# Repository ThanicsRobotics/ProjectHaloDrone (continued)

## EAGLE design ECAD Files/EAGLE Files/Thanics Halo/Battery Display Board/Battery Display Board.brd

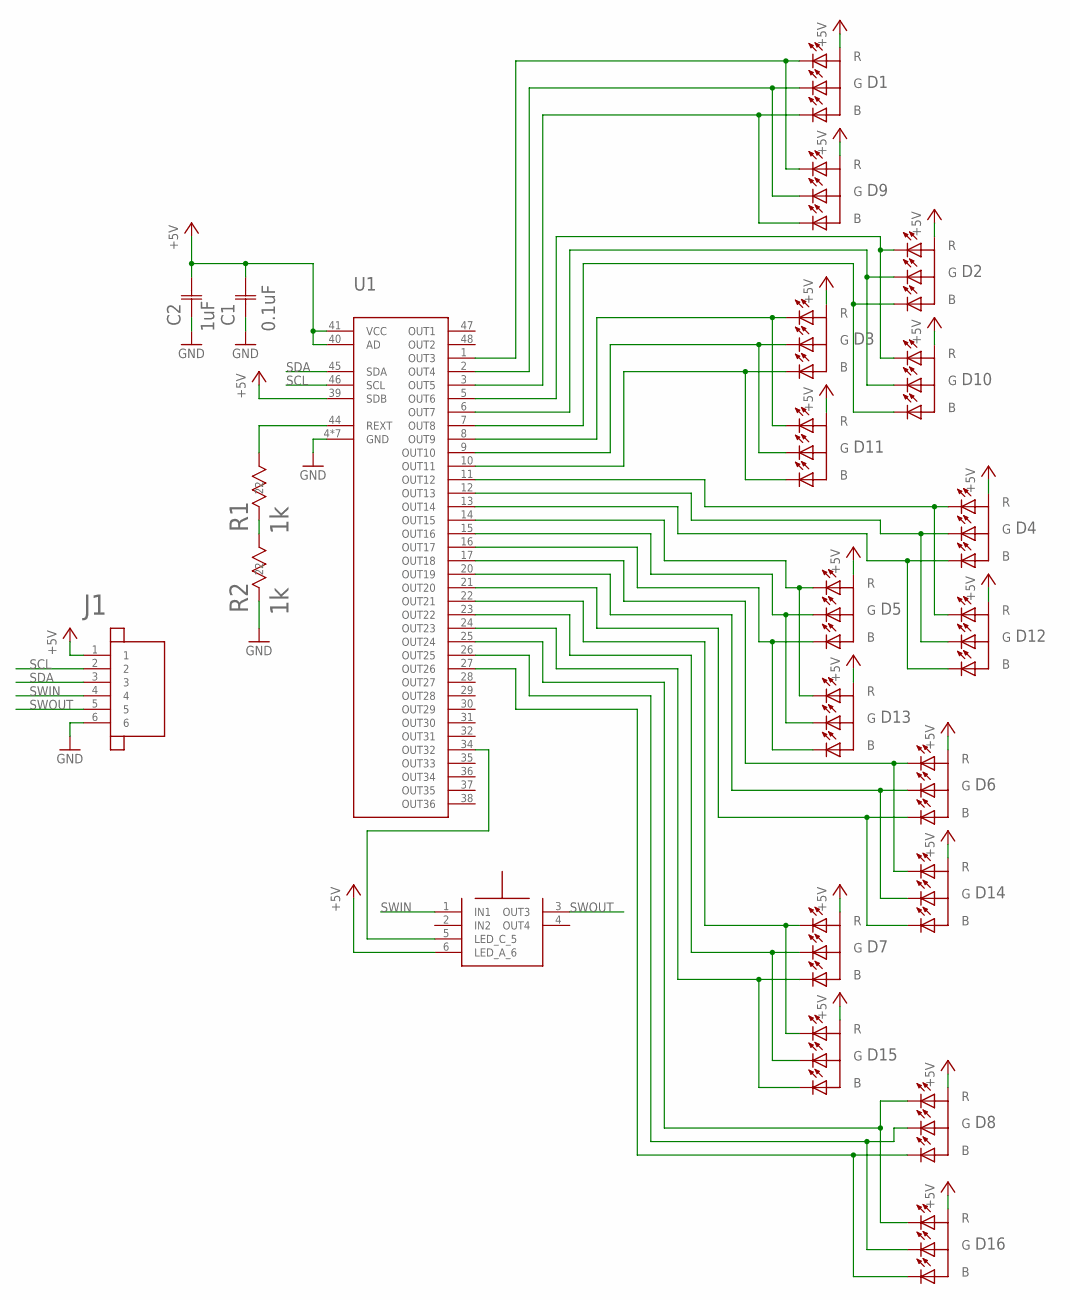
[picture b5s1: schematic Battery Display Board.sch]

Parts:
C1: 0.1uF; 0805
C2: 1uF; YAG_CC0805
D1, D2, D3, D4, D5, D6, D7, D8, D9, D10, D11, D12, D13, D14, D15, D16: ASMB-MTB0-0A3A2; ASMB-MTB0_LED
J1: JST_SH_6POS_SIDE
R1, R2: 1k; RC0603N-M
U1: IS31FL3236; TQFP-48
U$2: LED_TACT_SWITCH

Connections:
+5V: C1.2, C2.2 (22), D1.1 (A), D2.1 (A), D3.1 (A), D4.1 (A), D5.1 (A), D6.1 (A), D7.1 (A), D8.1 (A), D9.1 (A), D10.1 (A), D11.1 (A), D12.1 (A), D13.1 (A), D14.1 (A), D15.1 (A), D16.1 (A), J1.1, U1.39 (SDB), U1.40 (AD), U1.41 (VCC), U$2.6 (LED_A_6)
GND: C1.1, C2.1 (11), J1.6, R2.2 (22), U1.4 (GND), U1.18 (GND), U1.19 (GND), U1.33 (GND), U1.42 (GND), U1.43 (GND), U1.EP (GND)
unnamed: D1.4 (R), D9.4 (R), U1.1 (OUT3)
unnamed: D1.3 (G), D9.3 (G), U1.2 (OUT4)
unnamed: D2.3 (G), D10.3 (G), U1.6 (OUT7)
unnamed: D1.2 (B), D9.2 (B), U1.3 (OUT5)
unnamed: D2.4 (R), D10.4 (R), U1.5 (OUT6)
unnamed: R1.1 (11), U1.44 (REXT)
unnamed: D3.4 (R), D11.4 (R), U1.8 (OUT9)
unnamed: D3.3 (G), D11.3 (G), U1.9 (OUT10)
unnamed: D3.2 (B), D11.2 (B), U1.10 (OUT11)
unnamed: D4.4 (R), D12.4 (R), U1.11 (OUT12)
unnamed: D4.3 (G), D12.3 (G), U1.12 (OUT13)
unnamed: D4.2 (B), D12.2 (B), U1.13 (OUT14)
unnamed: D5.4 (R), D13.4 (R), U1.14 (OUT15)
unnamed: D5.3 (G), D13.3 (G), U1.15 (OUT16)
unnamed: D5.2 (B), D13.2 (B), U1.16 (OUT17)
unnamed: D6.4 (R), D14.4 (R), U1.17 (OUT18)
unnamed: D6.3 (G), D14.3 (G), U1.20 (OUT19)
unnamed: D6.2 (B), D14.2 (B), U1.21 (OUT20)
unnamed: D7.4 (R), D15.4 (R), U1.22 (OUT21)
unnamed: D7.3 (G), D15.3 (G), U1.23 (OUT22)
unnamed: D7.2 (B), D15.2 (B), U1.24 (OUT23)
unnamed: D8.4 (R), D16.4 (R), U1.25 (OUT24)
unnamed: D8.3 (G), D16.3 (G), U1.26 (OUT25)
unnamed: D8.2 (B), D16.2 (B), U1.27 (OUT26)
unnamed: D2.2 (B), D10.2 (B), U1.7 (OUT8)
unnamed: R1.2 (22), R2.1 (11)
unnamed: U1.34 (OUT32), U$2.5 (LED_C_5)
SCL: J1.2, U1.46 (SCL)
SDA: J1.3, U1.45 (SDA)
SWIN: J1.4, U$2.1 (IN1)
SWOUT: J1.5, U$2.3 (OUT3)

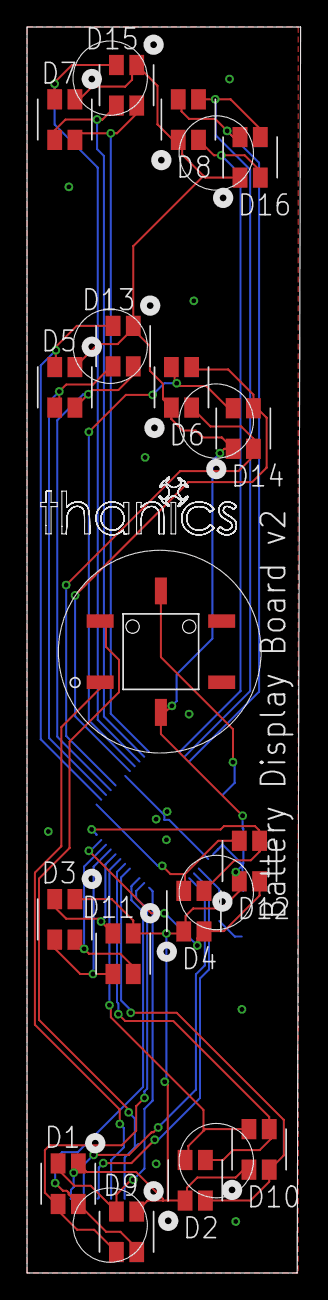
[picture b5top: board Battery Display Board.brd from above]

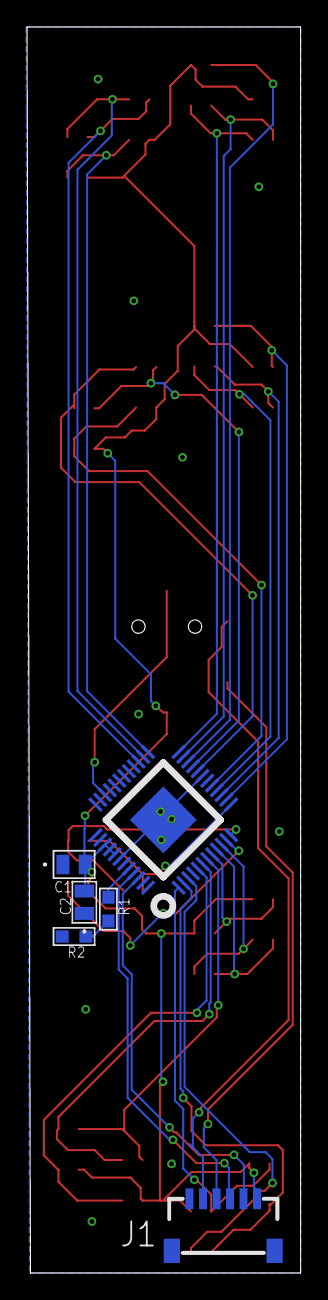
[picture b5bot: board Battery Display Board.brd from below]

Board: 2 copper layers, 20.2 x 92.2 mm, 23 parts (6 on the bottom side), 33 nets.

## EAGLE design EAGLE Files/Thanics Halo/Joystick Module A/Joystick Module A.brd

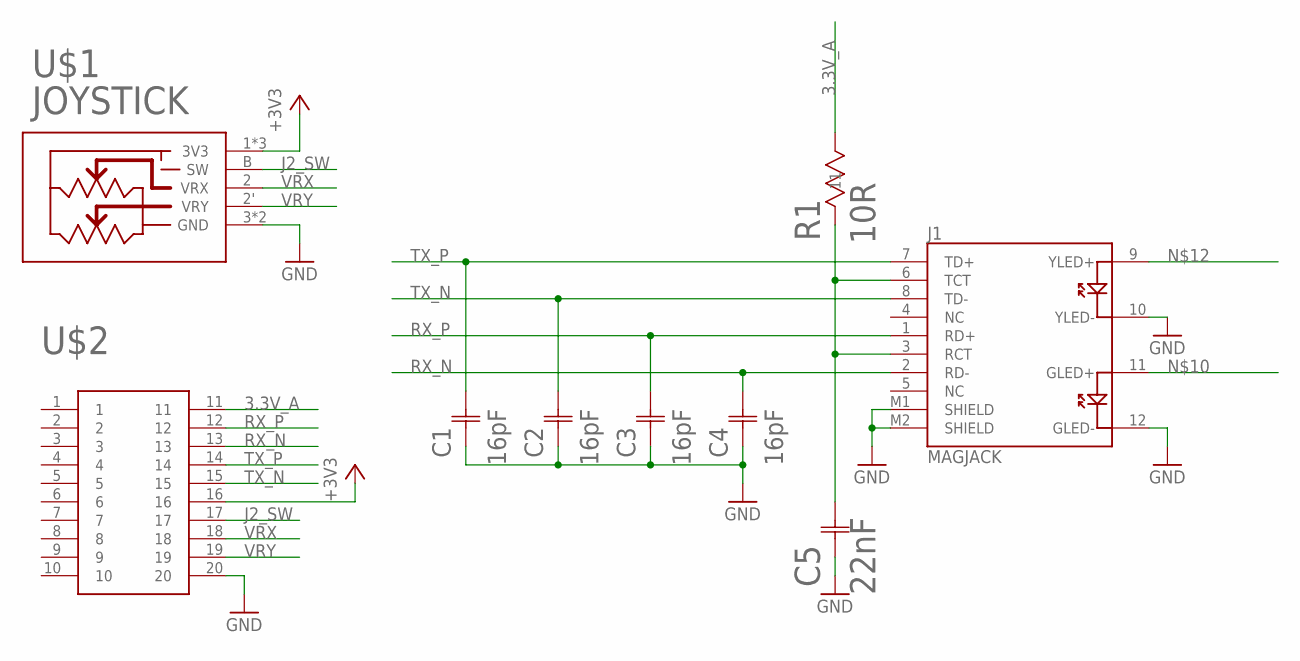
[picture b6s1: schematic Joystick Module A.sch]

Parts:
C1, C2, C3, C4: 16pF; G-155-M
C5: 22nF; G-155-M
J1: MAGJACK
R1: 10R; STA_RNCP0805-M
U$1: JOYSTICK"; JOYSTICK
U$2: EDGE_CONNECTOR_20POS_CONTACTS

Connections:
3.3V_A: R1.2 (22), U$2.11
+3V3: U$1.1 (3V3), U$1.1' (3V3), U$1.A (3V3), U$2.16
GND: C1.1 (11), C2.1 (11), C3.1 (11), C4.1 (11), C5.1 (11), J1.10 (YLED-), J1.12 (GLED-), J1.M1 (SHIELD), J1.M2 (SHIELD), U$1.3 (GND), U$1.3' (GND), U$2.20
J2_SW: U$1.B (SW), U$2.17
unnamed: C5.2 (22), J1.3 (RCT), J1.6 (TCT), R1.1 (11)
RX_N: C4.2 (22), J1.2 (RD-), U$2.13
RX_P: C3.2 (22), J1.1 (RD+), U$2.12
TX_N: C2.2 (22), J1.8 (TD-), U$2.15
TX_P: C1.2 (22), J1.7 (TD+), U$2.14
VRX: U$1.2 (VRX), U$2.18
VRY: U$1.2' (VRY), U$2.19

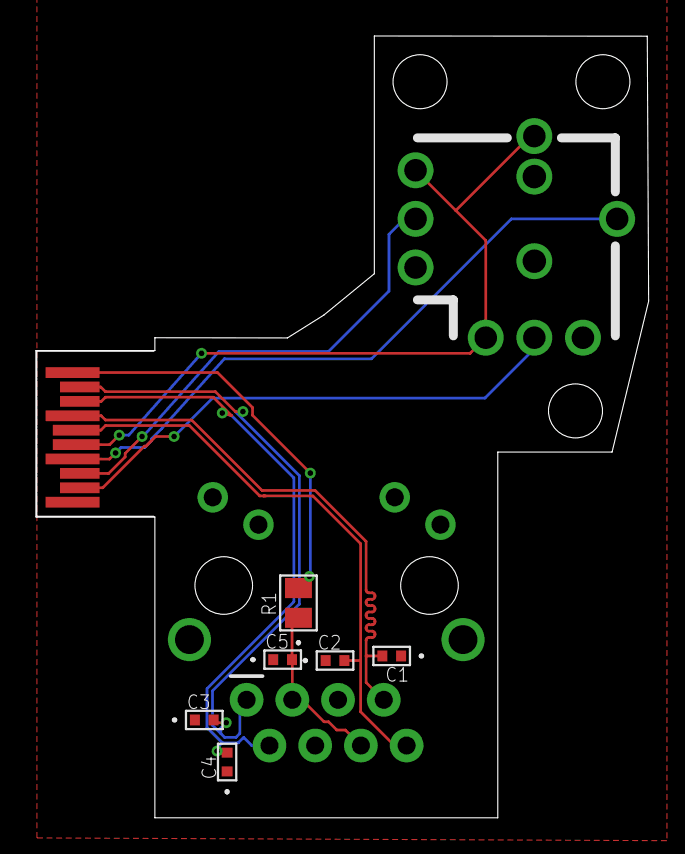
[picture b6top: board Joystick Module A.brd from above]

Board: 2 copper layers, 34.0 x 43.4 mm, 9 parts (1 on the bottom side), 11 nets.

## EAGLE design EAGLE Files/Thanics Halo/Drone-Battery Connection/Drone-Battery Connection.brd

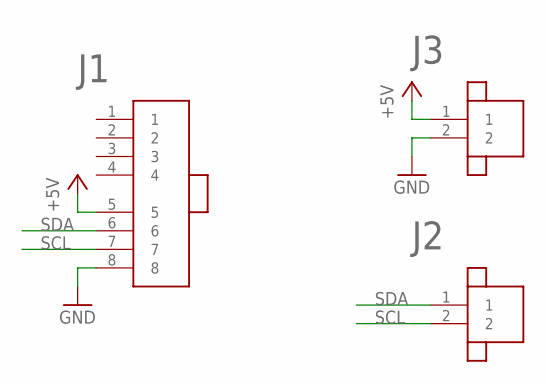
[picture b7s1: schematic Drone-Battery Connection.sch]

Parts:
J1: SPRING_BTB_8POS_MALE
J2, J3: JST_SH_2POS

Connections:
+5V: J1.5, J3.1
GND: J1.8, J3.2
SCL: J1.7, J2.2
SDA: J1.6, J2.1

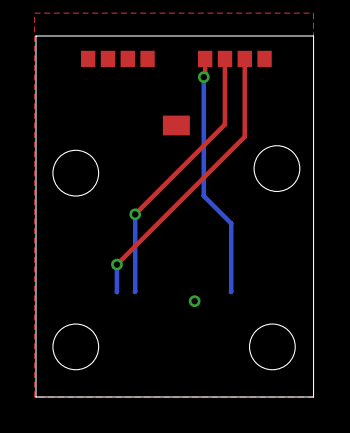
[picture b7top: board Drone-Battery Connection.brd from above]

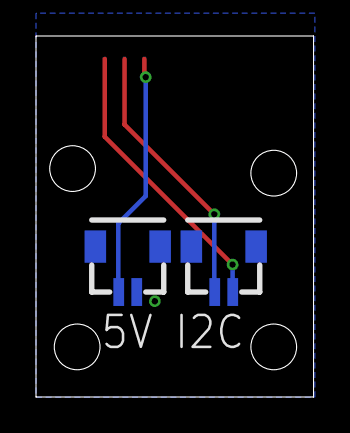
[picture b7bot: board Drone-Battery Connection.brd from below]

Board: 2 copper layers, 15.4 x 20.1 mm, 3 parts (2 on the bottom side), 4 nets.

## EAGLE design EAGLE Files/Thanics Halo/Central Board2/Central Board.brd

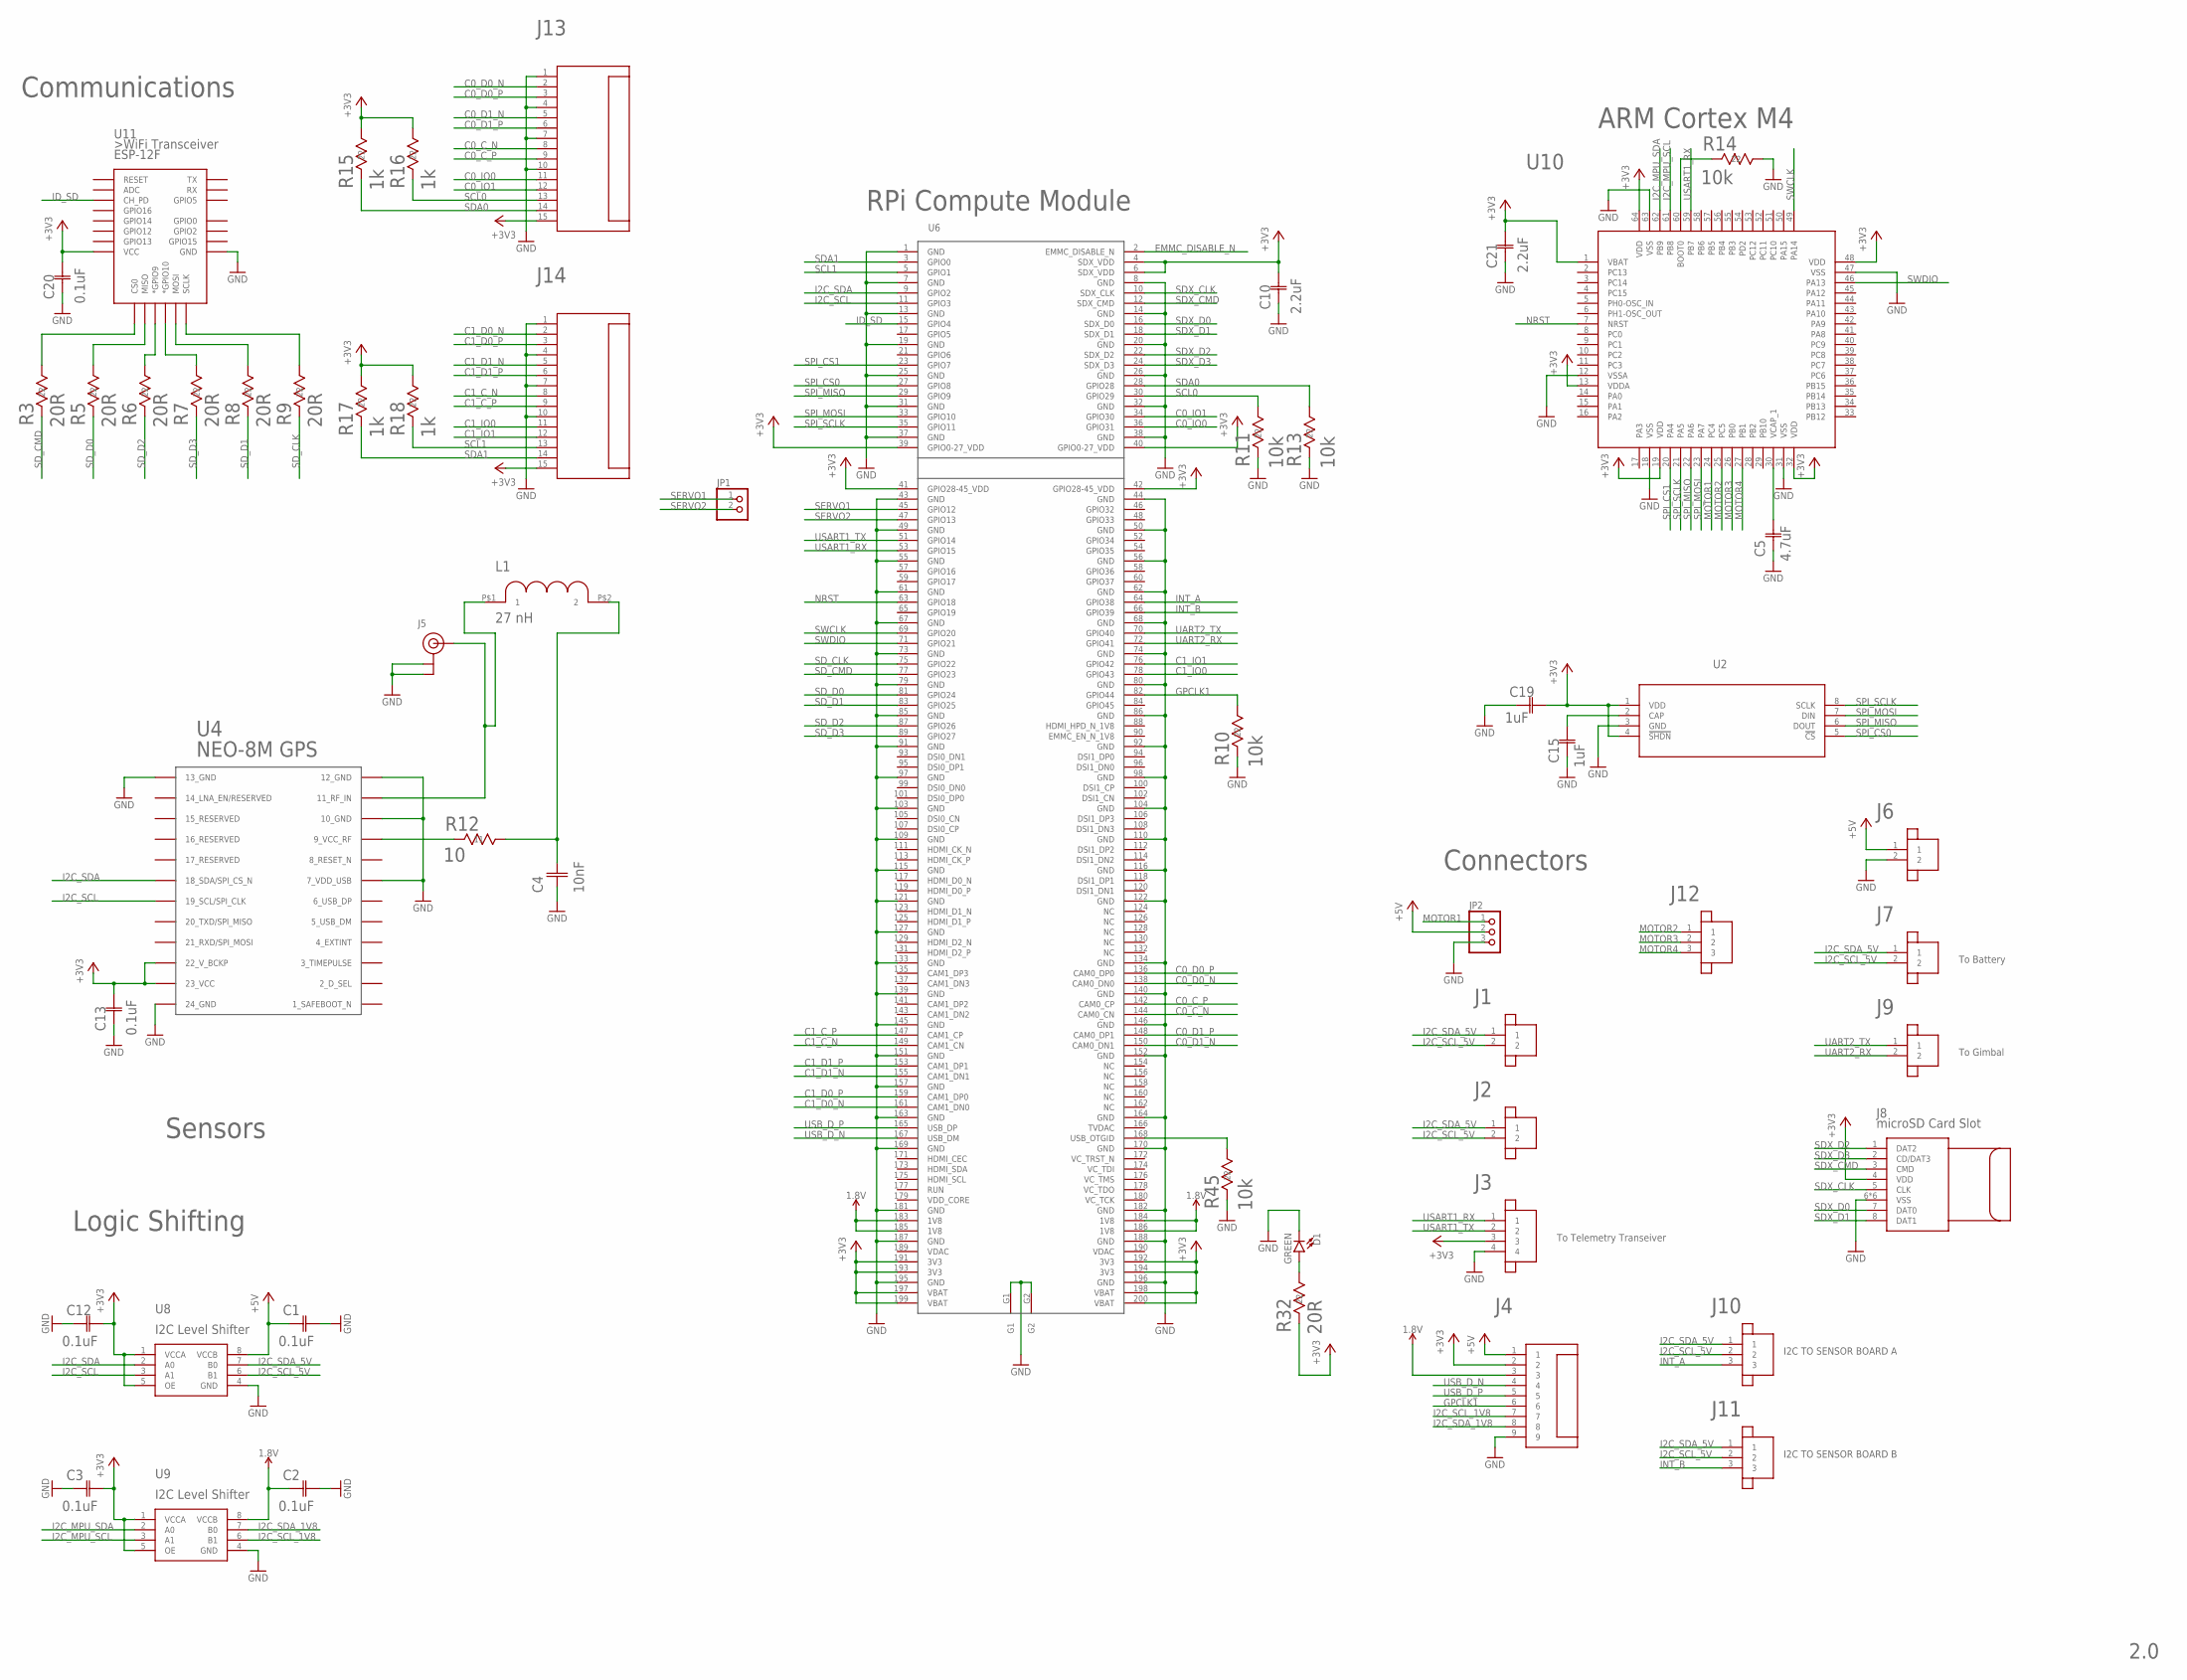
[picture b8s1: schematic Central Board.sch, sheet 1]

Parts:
C1, C2, C3, C12, C13, C20: 0.1uF; 0805
C4: 10nF; 0603_CAPACITOR
C5: 4.7uF; 0603-M
C10, C21: 2.2uF; G-188-M
C15, C19: 1uF; YAG_CC0805
D1: GREEN; LED-0603
J1, J2, J6, J7, J9: JST_SH_2POS
J3: JST_SH_4POS
J4: 9POS_FFC_CONNECTOR
J5: U.FL
J8: MICROSD
J10, J11, J12: JST_SH_3POS
J13, J14: 0526101572_15ZIF_CONNECTOR; 15POS_FFC_CONNECTOR
JP1: PINHD-1X2; 1X02
JP2: PINHD-1X3; 1X03
L1: 27 nH; 0402_INDUCTOR
R3, R5, R6, R7, R8, R9, R32: 20R; RC0603N-M
R10, R11, R13, R14, R45: 10k; RC0805N
R12: 10; STA_RNCP0805-M
R15, R16, R17, R18: 1k; RC0603N-M
U2: MPL115A1LGA8-M; LGA8-M
U4: NEO-M8
U6: COMPUTE_MODULE; SO-DIMM
U8, U9: FXMAR2102; 8-UMLP
U10: STM32F446; LQFP64
U11: ESP12ESMD; ESP12E-SMD

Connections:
1.8V: C2.1, J4.3, U6.183 (1V8), U6.184 (1V8), U6.185 (1V8), U6.186 (1V8), U9.8 (VCCB); also elsewhere on the board
+3V3: C3.2, C10.2 (22), C12.2, C13.2, C19.2 (22), C20.2, C21.2 (22), J3.3, J4.2, J8.4 (VDD), J13.15, J14.15, R15.1 (11), R16.1 (11), R17.1 (11), R18.1 (11), R32.2 (22), U2.1 (VDD), U2.4 (!SHDN), U4.22 (22_V_BCKP), U4.23 (23_VCC), U6.4 (SDX_VDD), U6.6 (SDX_VDD), U6.39 (GPIO0-27_VDD), U6.40 (GPIO0-27_VDD), U6.41 (GPIO28-45_VDD), U6.42 (GPIO28-45_VDD), U6.191 (3V3), U6.192 (3V3), U6.193 (3V3), U6.194 (3V3), U6.197 (VBAT), U6.198 (VBAT), U6.199 (VBAT), U6.200 (VBAT), U8.1 (VCCA), U8.5 (OE), U9.1 (VCCA), U9.5 (OE), U10.1 (VBAT), U10.13 (VDDA), U10.19 (VDD), U10.32 (VDD), U10.48 (VDD), U10.64 (VDD), U11.VCC; also elsewhere on the board
+5V: C1.1, J4.1, J6.1, JP2.2, U8.8 (VCCB); also elsewhere on the board
C0_C_N: J13.8, U6.144 (CAM0_CN)
C0_C_P: J13.9, U6.142 (CAM0_CP)
C0_D0_N: J13.2, U6.138 (CAM0_DN0)
C0_D0_P: J13.3, U6.136 (CAM0_DP0)
C0_D1_N: J13.5, U6.150 (CAM0_DN1)
C0_D1_P: J13.6, U6.148 (CAM0_DP1)
C0_IO0: J13.11, U6.36 (GPIO31)
C0_IO1: J13.12, U6.34 (GPIO30)
C1_C_N: J14.8, U6.149 (CAM1_CN)
C1_C_P: J14.9, U6.147 (CAM1_CP)
C1_D0_N: J14.2, U6.161 (CAM1_DN0)
C1_D0_P: J14.3, U6.159 (CAM1_DP0)
C1_D1_N: J14.5, U6.155 (CAM1_DN1)
C1_D1_P: J14.6, U6.153 (CAM1_DP1)
C1_IO0: J14.11, U6.78 (GPIO43)
C1_IO1: J14.12, U6.76 (GPIO42)
EMMC_DISABLE_N: U6.2 (EMMC_DISABLE_N)
GND: C1.2, C2.2, C3.1, C4.1, C5.1, C10.1 (11), C12.1, C13.1, C15.1 (11), C19.1 (11), C20.1, C21.1 (11), D1.C, J3.4, J4.9, J5.P$1 (GND), J5.P$2 (GND), J6.2, J8.6 (VSS), J8.9 (VSS), J8.10 (VSS), J8.11 (VSS), J8.12 (VSS), J8.13 (VSS), J13.1, J13.4, J13.7, J13.10, J14.1, J14.4, J14.7, J14.10, JP2.3, R10.2 (22), R11.2 (22), R13.2 (22), R14.1 (11), R45.2 (22), U2.3 (GND), U4.7 (7_VDD_USB), U4.10 (10_GND), U4.12 (12_GND), U4.13 (13_GND), U4.24 (24_GND), U6.1 (GND), U6.7 (GND), U6.8 (GND), U6.13 (GND), U6.14 (GND), U6.19 (GND), U6.20 (GND), U6.25 (GND), U6.26 (GND), U6.31 (GND), U6.32 (GND), U6.37 (GND), U6.38 (GND), U6.43 (GND), U6.44 (GND), U6.49 (GND), U6.50 (GND), U6.55 (GND), U6.56 (GND), U6.61 (GND), U6.62 (GND), U6.67 (GND), U6.68 (GND), U6.73 (GND), U6.74 (GND), U6.79 (GND), U6.80 (GND), U6.85 (GND), U6.86 (GND), U6.91 (GND), U6.92 (GND), U6.97 (GND), U6.98 (GND), U6.103 (GND), U6.104 (GND), U6.109 (GND), U6.110 (GND), U6.115 (GND), U6.116 (GND), U6.121 (GND), U6.122 (GND), U6.127 (GND), U6.133 (GND), U6.134 (GND), U6.139 (GND), U6.140 (GND), U6.145 (GND), U6.146 (GND), U6.151 (GND), U6.152 (GND), U6.157 (GND), U6.163 (GND), U6.164 (GND), U6.169 (GND), U6.170 (GND), U6.181 (GND), U6.182 (GND), U6.187 (GND), U6.188 (GND), U6.195 (GND), U6.196 (GND), U6.G1, U6.G2, U8.4 (GND), U9.4 (GND), U10.12 (VSSA), U10.18 (VSS), U10.31 (VSS), U10.47 (VSS), U10.63 (VSS), U11.GND; also elsewhere on the board
GPCLK1: J4.6, R10.1 (11), U6.82 (GPIO44)
I2C_MPU_SCL: U9.3 (A1), U10.61 (PB8)
I2C_MPU_SDA: U9.2 (A0), U10.62 (PB9)
I2C_SCL: U4.19 (19_SCL/SPI_CLK), U6.11 (GPIO3), U8.3 (A1)
I2C_SCL_1V8: J4.7, U9.6 (B1)
I2C_SCL_5V: J1.2, J2.2, J7.2, J10.2, J11.2, U8.6 (B1)
I2C_SDA: U4.18 (18_SDA/SPI_CS_N), U6.9 (GPIO2), U8.2 (A0)
I2C_SDA_1V8: J4.8, U9.7 (B0)
I2C_SDA_5V: J1.1, J2.1, J7.1, J10.1, J11.1, U8.7 (B0)
ID_SD: U6.15 (GPIO4), U11.CH_PD
INT_A: J10.3, U6.64 (GPIO38)
INT_B: J11.3, U6.66 (GPIO39)
MOTOR1: JP2.1, U10.24 (PC4)
MOTOR2: J12.1, U10.25 (PC5)
MOTOR3: J12.2, U10.26 (PB0)
MOTOR4: J12.3, U10.27 (PB1)
unnamed: J5.P$3 (SIGNAL), L1.P$1 (1), U4.11 (11_RF_IN)
unnamed: D1.A, R32.1 (11)
unnamed: R3.1 (11), U11.CS0
unnamed: R5.1 (11), U11.MISO
unnamed: R6.1 (11), U11.GPIO9 (*GPIO9)
unnamed: R7.1 (11), U11.GPIO10 (*GPIO10)
unnamed: C5.2, U10.30 (VCAP_1)
unnamed: C15.2 (22), U2.2 (CAP)
unnamed: R12.1 (11), U4.9 (9_VCC_RF)
unnamed: R8.1 (11), U11.MOSI
unnamed: R9.1 (11), U11.SCLK
unnamed: R14.2 (22), U10.60 (BOOT0)
unnamed: C4.2, L1.P$2 (2), R12.2 (22)
unnamed: R45.1 (11), U6.168 (USB_OTGID)
NRST: U6.63 (GPIO18), U10.7 (NRST)
SCL0: J13.13, R11.1 (11), R16.2 (22), U6.30 (GPIO29)
SCL1: J14.13, R18.2 (22), U6.5 (GPIO1)
SDA0: J13.14, R13.1 (11), R15.2 (22), U6.28 (GPIO28)
SDA1: J14.14, R17.2 (22), U6.3 (GPIO0)
SDX_CLK: J8.5 (CLK), U6.10 (SDX_CLK)
SDX_CMD: J8.3 (CMD), U6.12 (SDX_CMD)
SDX_D0: J8.7 (DAT0), U6.16 (SDX_D0)
SDX_D1: J8.8 (DAT1), U6.18 (SDX_D1)
SDX_D2: J8.1 (DAT2), U6.22 (SDX_D2)
SDX_D3: J8.2 (CD/DAT3), U6.24 (SDX_D3)
SD_CLK: R9.2 (22), U6.75 (GPIO22)
SD_CMD: R3.2 (22), U6.77 (GPIO23)
SD_D0: R5.2 (22), U6.81 (GPIO24)
SD_D1: R8.2 (22), U6.83 (GPIO25)
SD_D2: R6.2 (22), U6.87 (GPIO26)
SD_D3: R7.2 (22), U6.89 (GPIO27)
SERVO1: JP1.1, U6.45 (GPIO12)
SERVO2: JP1.2, U6.47 (GPIO13)
SPI_CS0: U2.5 (!CS), U6.27 (GPIO8)
SPI_CS1: U6.23 (GPIO7), U10.20 (PA4)
SPI_MISO: U2.6 (DOUT), U6.29 (GPIO9), U10.22 (PA6)
SPI_MOSI: U2.7 (DIN), U6.33 (GPIO10), U10.23 (PA7)
SPI_SCLK: U2.8 (SCLK), U6.35 (GPIO11), U10.21 (PA5)
SWCLK: U6.69 (GPIO20), U10.49 (PA14)
SWDIO: U6.71 (GPIO21), U10.46 (PA13)
UART2_RX: J9.2, U6.72 (GPIO41)
UART2_TX: J9.1, U6.70 (GPIO40)
USART1_RX: J3.1, U6.53 (GPIO15), U10.59 (PB7)
USART1_TX: J3.2, U6.51 (GPIO14)
USB_D_N: J4.4, U6.167 (USB_DM)
USB_D_P: J4.5, U6.165 (USB_DP)

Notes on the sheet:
I2C TO SENSOR BOARD A
I2C TO SENSOR BOARD B
To Telemetry Transeiver
To Battery
To Gimbal
Communications
RPi Compute Module
Sensors
Connectors
Logic Shifting
2.0
ARM Cortex M4

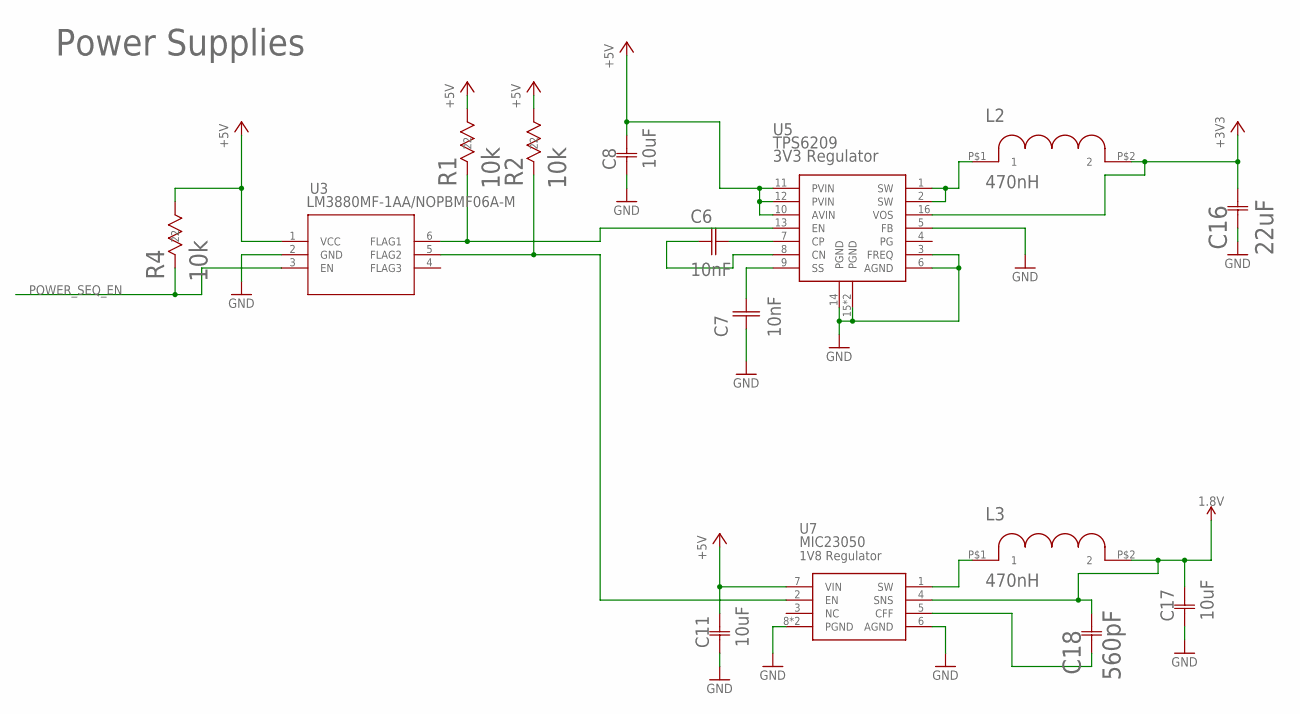
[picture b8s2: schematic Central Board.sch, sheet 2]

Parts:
C6, C7: 10nF; 0603_CAPACITOR
C8, C11, C17: 10uF; G-21
C16: 22uF; G-21
C18: 560pF; CC0402N-M
L2, L3: 470nH; 1008_INDUCTOR
R1, R2, R4: 10k; RC0805N
U3: LM3880MF-1AA/NOPBMF06A-M; MF06A-M
U5: TPS6209; VQFN16
U7: MIC23050; MLF(ML)_8PIN

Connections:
1.8V: C17.2 (22), C18.2 (22), L3.P$2 (2), U7.4 (SNS); also elsewhere on the board
+3V3: C16.2 (22), L2.P$2 (2), U5.16 (VOS); also elsewhere on the board
+5V: C8.2 (22), C11.2 (22), R1.1 (11), R2.1 (11), R4.1 (11), U3.1 (VCC), U5.10 (AVIN), U5.11 (PVIN), U5.12 (PVIN), U7.7 (VIN); also elsewhere on the board
GND: C7.1, C8.1 (11), C11.1 (11), C16.1 (11), C17.1 (11), U3.2 (GND), U5.3 (FREQ), U5.5 (FB), U5.6 (AGND), U5.14 (PGND), U5.15 (PGND), U5.17 (PGND), U7.6 (AGND), U7.8 (PGND), U7.EP (PGND); also elsewhere on the board
unnamed: C6.2, U5.7 (CP)
unnamed: C6.1, U5.8 (CN)
unnamed: R1.2 (22), U3.6 (FLAG1), U5.13 (EN)
unnamed: R2.2 (22), U3.5 (FLAG2), U7.2 (EN)
unnamed: C7.2, U5.9 (SS)
unnamed: L2.P$1 (1), U5.1 (SW), U5.2 (SW)
unnamed: L3.P$1 (1), U7.1 (SW)
unnamed: C18.1 (11), U7.5 (CFF)
POWER_SEQ_EN: R4.2 (22), U3.3 (EN)

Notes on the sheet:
Power Supplies

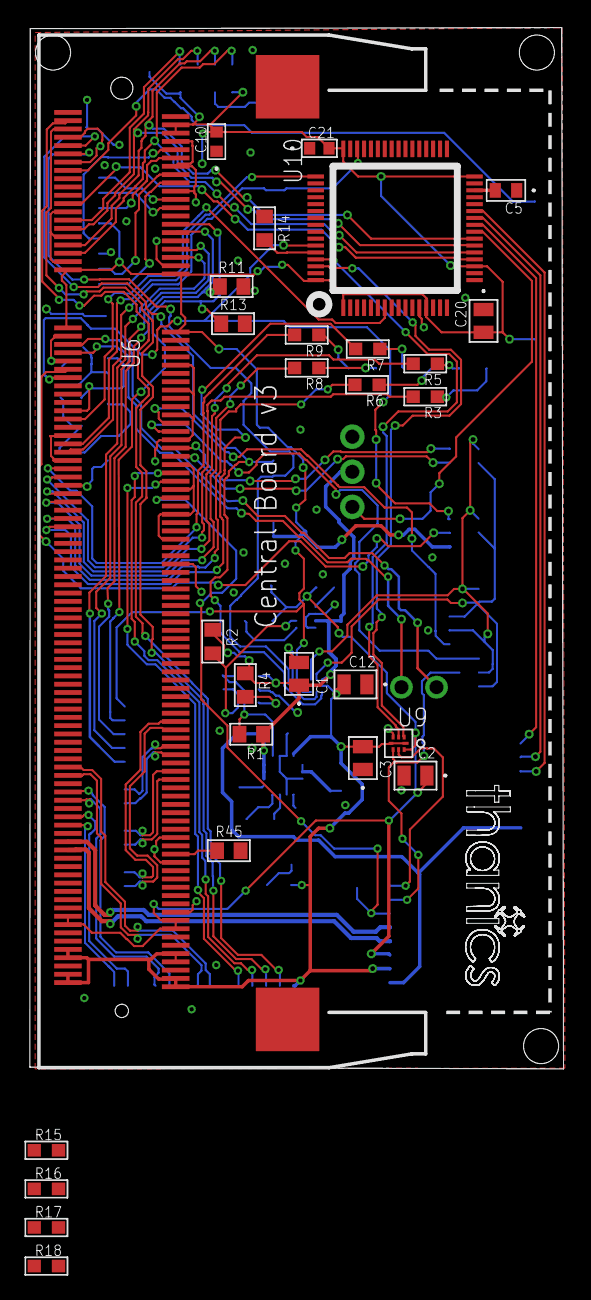
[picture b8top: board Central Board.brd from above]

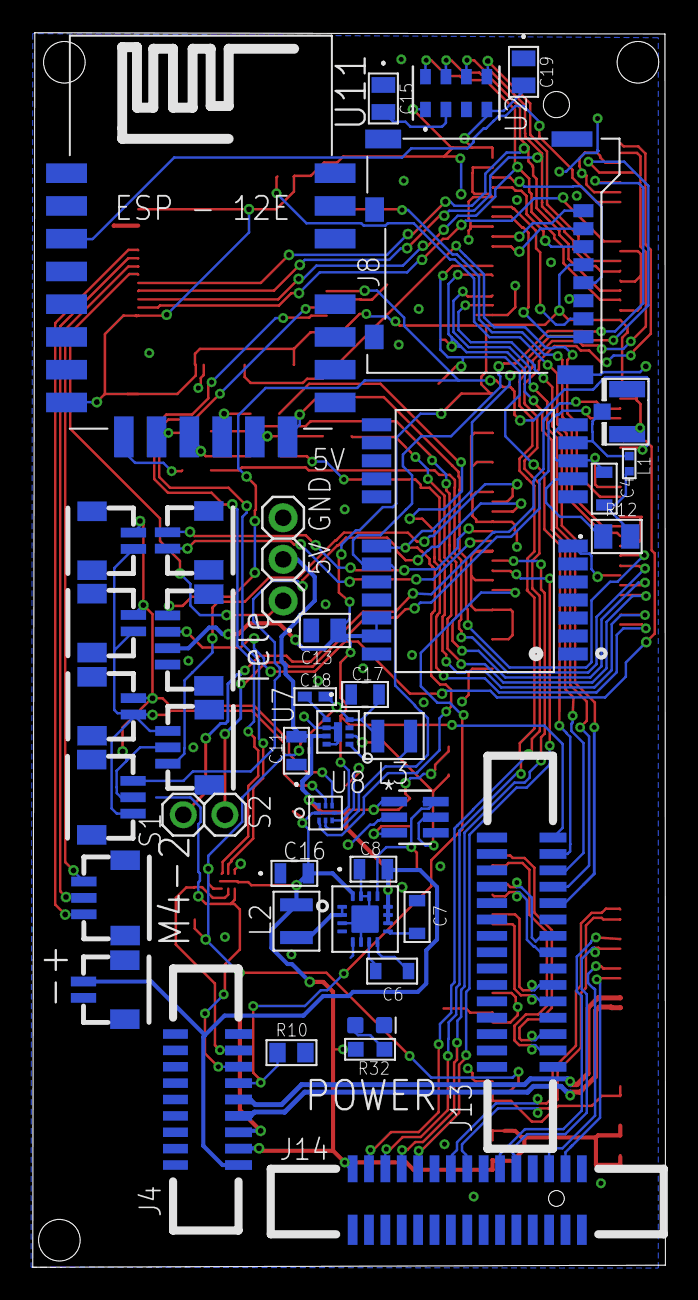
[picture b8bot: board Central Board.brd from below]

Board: 2 copper layers, 38.6 x 75.4 mm, 69 parts (41 on the bottom side), 91 nets.

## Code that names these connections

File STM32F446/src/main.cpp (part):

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// Sends all motor PWM signals LOW
void motors_off()
{
  motor1 = 0;
  motor2 = 0;
  motor3 = 0;
  motor4 = 0;
}

// Sends all motor PWM signals HIGH
void motors_on()
{
  motor1 = 1;
  motor2 = 1;
  motor3 = 1;
  motor4 = 1;
}

// void readline() {
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    {
      esc_loop_timer = onTime.read_us(); // Read the current time.
      if (timer_channel_1 <= esc_loop_timer)
        motor1 = 0; // Set digital output 7 to low if the time is expired.
      if (timer_channel_2 <= esc_loop_timer)
        motor2 = 0; // Set digital output 6 to low if the time is expired.
      if (timer_channel_3 <= esc_loop_timer)
        motor3 = 0; // Set digital output 5 to low if the time is expired.
      if (timer_channel_4 <= esc_loop_timer)
        motor4 = 0; // Set digital output 4 to low if the time is expired.
    }
  }
}
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
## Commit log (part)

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2018-02-11 switched rates to angle pos
2018-02-11 restored rest of program
2018-02-12 added back ultrasonic data
2018-02-12 testing
2018-02-12 readded gitignore
2018-02-12 testing whoami
2018-02-12 testing gyro
2018-02-12 restored main program
2018-02-13 moved serial close
2018-02-13 added debug
2018-02-13 added more messages in shutdown
2018-02-13 added opening port messages
2018-02-13 changed variable declaration
2018-02-13 switched wiringserial to pigpio serial
2018-02-13 removed wiringpi functions
2018-02-13 pigpio serial test
2018-02-13 added initialize
2018-02-13 changed port address
2018-02-13 changed syntax
2018-02-13 added debug message
2018-02-13 increased repetitions
2018-02-13 added fflush
2018-02-14 added i2c to serial test
2018-02-14 added wiringpi setup
2018-02-14 removed i2c from serialtest
2018-02-14 reformated serialtest
2018-02-14 added error handling
2018-02-14 added unsigned
2018-02-14 removed unsigned
2018-02-14 changed " to '
2018-02-14 removed error if statement
2018-02-14 added read line
2018-02-14 added i2c
2018-02-14 added string to int conv
2018-02-15 fixed thischar
2018-02-16 added filepath to cfg files
2018-02-16 added absolute path
2018-02-16 modified reset.cfg
2018-02-16 reformated project and added pid and spi files
2018-02-16 added more includes
2018-02-16 fixed file paths
2018-02-17 modified debug message
2018-02-17 added endl
2018-02-17 added throttle transmission to STM32
2018-02-17 removed sendthrottle from main loop
2018-02-17 added quadcopter self-arm
2018-02-17 forgot ;
2018-02-17 added armed condition
2018-02-17 testing STM32 receiving throttle
2018-02-18 added delay
2018-02-18 moved armed setting
2018-02-18 added run condition to arm while loop
2018-02-18 testing spi
2018-02-18 added makefile and reorganized project
2018-02-18 fixed makefile
2018-02-18 changed makefile
2018-02-18 modified makefile
2018-02-18 fixed pathing
2018-02-18 changed string adding
2018-02-18 added iostream include
2018-02-18 fixed strings
2018-02-18 changed arming process
2018-02-18 removed const
2018-02-18 forgot to compile
2018-02-18 modified self-arm
2018-02-18 testing throttle
2018-02-18 testing angles
2018-02-18 fixed arming conditionals
2018-02-18 added getpid
2018-02-18 added library
2018-02-19 optimized wait loop
2018-02-19 added hz debug
2018-02-19 fixed looprate
2018-02-19 changed spi read conditions
2018-02-19 modified spi read
2018-02-19 forgot to change header
2018-02-19 printing binary value
2018-02-19 fixed spi write data structure
2018-02-19 changed back to int
2018-02-19 added print binary
2018-02-19 removed binary printing, added back real angles
2018-02-20 implemented altitude hold
2018-02-20 increased pulse delay
2018-02-20 added wait motor signal
2018-02-21 removed motor signals from auth
2018-02-21 added back filter
2018-02-21 fixed pid
2018-02-21 added prestart
2018-02-21 added declaration
2018-02-21 removed pre start
2018-02-21 removed ultrasonic
2018-02-21 removed arming
2018-02-21 removed conditional while loop
2018-02-21 added back arming
2018-02-21 added volatile to several global vars
2018-02-21 reformatted auth loop
2018-02-21 removed setting armed to false
2018-02-21 increased gyro cal timeout
2018-02-21 hard set throttle and fixed spi reply
2018-02-21 removed get throttle
2018-02-21 increased throttle
2018-02-21 removed conditional motor start
2018-02-21 fixed auth handling
2018-02-21 added back spi
2018-02-21 changed spi conditions
2018-02-22 changed loop time back to 4000
2018-02-22 decreased frequency of spi read/write
2018-02-22 changed throttle calculation
2018-02-22 fixed gyro calibration
2018-02-22 fixed gyro cal
2018-02-22 reverted back to angle roll
2018-02-22 changed height distance
2018-02-22 testing gyro send
2018-02-22 changed from gyro to acc
2018-02-22 moved calculate angles
2018-02-22 isolated gyro code
2018-02-22 fixed if else statement
2018-02-22 changed spi read to xfer
2018-02-22 fixed casting
2018-02-22 changed pwr management reg to 0
2018-02-22 restored old gyro cal
2018-02-22 changed to angles
2018-02-22 added back gyro filter
2018-02-23 fixed stuck arming loop
2018-02-23 testing i2c
2018-02-23 changed include
2018-02-23 changed gyro cal
2018-02-24 added back ultrasonic rangefinding
2018-02-24 decreased pulse delay
2018-02-24 changed ultrasonic timing
2018-02-24 enabled stopping motors
2018-02-24 set arm at end of controller arm sequence
2018-02-24 fixed throttle input
2018-02-25 added readline functionality to serial
2018-02-25 removed readchar loop
2018-02-25 removed delay
2018-02-25 handled throttle input = 0
2018-02-25 added motor test
2018-02-25 fixed test motors
2018-02-25 fixed serial
2018-02-25 allowed zeros in ultrasonic code
2018-02-25 added no motor functionality
2018-02-25 added setaltitude declaration
2018-02-25 added break
2018-02-25 fixed decrease altitude
2018-02-25 fixed scaling
2018-03-02 added vl53l1 api
2018-03-02 added laser file
2018-03-04 added functions to ranging_sensor_comms
2018-03-09 cleaned out unused functions
2018-03-09 modified platform file for I2C commands
2018-03-09 fixed typo
2018-03-10 Reorganized directories and added Makefiles
2018-03-10 added a space in tab size
2018-03-10 changed -I to -B
2018-03-10 removed paths
2018-03-10 changed spaces to tabs
2018-03-10 removed spaces
2018-03-10 changed " to <
2018-03-11 removed dirs
2018-03-11 changed PATH to PROJPATH
2018-03-11 forgot ; and moved i2cfd
2018-03-11 changed includes to <>
2018-03-11 changed i2cfd in main.cpp
2018-03-11 changed i2c address pointer and added status definition
2018-03-11 added make clean functionality
2018-03-11 moved halo exec compilation to outer Makefile
2018-03-12 uncommented defines
2018-03-12 fixed spelling/variable misuse
2018-03-12 improved make clean, added -f to rm
2018-03-12 fixed Makefiles
2018-03-12 fixed pathing on Makefile
2018-03-12 removed unused Makefile variables
2018-03-12 added +
2018-03-12 switch cpp to c on dir2 and 3
2018-03-12 added back libs
2018-03-12 added missing functions
2018-03-13 commented out gpio functions
2018-03-13 implemented lasers in main.cpp
2018-03-13 added api includes
2018-03-13 added back compiled stm32 code
2018-03-13 added conditional laser closing
2018-04-03 removed vl53l1 api and code, and added updater program
2018-04-08 Added stream, camera and altitude files
2018-04-13 updated atmega updater code
2018-04-13 added stm32f446 firmware
2018-04-13 fixed stm32f446 reset
2018-04-13 fixed altitude variables
2018-04-13 fixed string library
2018-04-13 added std:: to string declarations
2018-04-13 removed redefinition of camera,receiver
2018-04-14 removed libs building from top makefile
2018-04-14 added extern back to camera,receiver
2018-04-14 fixed barometer address
2018-04-19 moved mavlink and added gps code
2018-04-20 removed ultrasonic code, fixed spi gyro calibration notice
2018-04-20 added radio to main.cpp and fixed shutdown commands
2018-04-20 fixed syntax errors
2018-04-20 fixed syntax and removed serial
2018-04-20 Added NemaTode lib, credits page
2018-04-20 fixed barometer registers/calculations
2018-04-20 added takereading function
2018-04-20 printing binary for testing
2018-04-20 changed altitude calculation for twos complement
2018-04-21 added barometer calibration
2018-04-21 fixed baro calibration
2018-04-21 added offset register setting
2018-04-21 added network streaming
2018-04-22 expanded streaming functions
2018-04-22 remove receive loop for receive on demand scheme
2018-04-23 added test for send/receive streaming
2018-04-24 integrated tcp socket with mavlink
2018-04-24 added buffer struct, added more debug messages
2018-04-24 changed gps read, disabled stream for now
2018-04-24 integrated nmeaparser
2018-04-24 added filter to nmea sentence
2018-04-24 added missing libraries/fixed syntax
2018-04-25 testing to find out nmea message size
2018-04-25 updated gps read to reading block data
2018-04-26 added other gps nmea message types and removed motor start when arming
2018-04-27 added return GPSService type
2018-04-28 added message structs and added gpsservice return
2018-04-28 added ncurses for debugging
2018-04-28 reorganized stream class
2018-04-28 added back sending gyro position
2018-04-29 changed arming scheme, added disarm
2018-04-29 removed "using namespace" from most files, added more debug printing
2018-04-29 trying to fix program exit problem, making thread joining cleaner
2018-04-29 fixing arm/disarm of stm32, made incoming data unsigned
2018-04-30 added menu selection
2018-04-30 added wrefeshes
2018-04-30 added back serial.cpp/h and changed motor code to run only 1 motor
2018-04-30 wrong motor
2018-05-01 refactored serial code into class, refactered gui, added fcmessage pack
2018-05-07 fixed serial 'this' usage and other syntax
2018-05-07 added serial mavlink testing
2018-05-07 fixes syntax errors
2018-05-07 refactored endwin into gui closeGUI
2018-05-07 added gui active indicator
2018-05-10 removed fail debug statement, redundant variable declarations
2018-05-11 fixed pathing in cpp and makefiles, and trying to use std::unique_ptr
2018-05-11 changed to c++17 and got heartbeat mavlink working
2018-05-12 Created FlightController and Radio classes, merged pid with FC
2018-05-12 Added Barometer class and implemented pi > STM32 message sending
2018-05-18 Started adding doxygen commenting
2018-05-19 Fixed class refactoring in GPS, added receive thread
2018-05-22 Implemented new radio protocol since mavlink too slow for real time
2018-05-22 fixed barometer thread error, made sure that thread joined up with main
2018-05-22 moved mavlink to libs, added more documentation
2018-05-22 continued refactoring main.cpp into helper
2018-05-23 fixed syntax errors from refactoring
2018-05-23 Modified STM32 interface, added more documentation.
2018-05-26 changed shutdown scheme, adopted RAII strategy with objects
2018-05-28 Optimizing shutdown and fixed minor bugs, trying to get gdb to work
2018-06-10 Refactored code, split FlightController into another class FCInterface
2018-06-12 fixed most compiler errors, added ThetaV and PTP functionality
2018-06-12 fixed all compiler/linker errors, libptp2 is now integrated into code
2018-06-15 removed mavlink for now, made shutdown raw ptr into shared_ptr
2018-06-16 changed data sharing strategy, passed by ref through setPWMInputs()
2018-06-18 finished install script
2018-06-20 added videostream (for gstreamer streaming) and tofsensor files
2018-06-22 removed libncurses from makefile, added gstreamer command to videostream
2018-06-29 implemented gstreamer transmitter pipeline, works
2018-06-30 Implemented recording while streaming
2018-07-04 added startFlightController to HaloController Added more libraries to install script
2018-07-14 added setSettings and moved gstinit to videostreamcontroller
2018-07-15 removed battery control code, added boost.asio version of streaming code
2018-07-15 Phase out reading
2018-07-16 separated radio types into different files, implemented WLAN radio Changed Stream to WLAN
2018-07-18 packet decode/encode working between drone and controller
2018-07-18 Reporting functionality
2018-07-19 Read and write to regsters
2018-07-19 read and write to register
2018-07-19 Added OPT3101 SDK
2018-07-19 edited/created makefiles for opt3101 library, disabled opt3101 serialLib changed .cc files to .cpp
2018-07-19 What I now learned is useful
2018-07-19 I meant useless
2018-07-19 restructured gimbalpackets and added SetAngles command
2018-07-22 Added more maneuver code/restructured
2018-07-22 added landing maneuver (unfinished)
2018-07-22 added crc check to control radio protocol, finished landing maneuver
2018-07-25 migrated wlan write code from controller to drone
2018-07-25 added new configuration file
2018-07-28 removed serial lib and added default constructors where necessary
2018-08-01 Clean Tree
2018-08-01 Did that work
2018-08-01 Okay let's try again
2018-08-02 revised boost install command and controller server hostname
2018-08-04 OPT3101 FrameData
2018-08-04 removed STDIOLIB
2018-08-04 deleted useless
2018-08-04 Get ready for this redesign!! HYPE!!!
2018-08-04 added hostcontroller as member variable instead of global changed rest of library to account for change
2018-08-05 filePath changed to /home/pi/
2018-08-05 letsgetit instance for capture/report. Distance added in Functions.cpp.
2018-08-06 fixed frameData usage
